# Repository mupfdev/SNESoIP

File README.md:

# SNESoIP: The SNES Wi-Fi adapter

## Status

In the first revisions I made some design flaws.  Looking back, it's
difficult for me to understand why it worked so well.  However, this
time I want to make it technically correct.  Therefore is the project is
currently in a state of re-design.

## Introduction

The SNESoIP (SNES over IP) is a Wi-Fi adapter for the Super Nintendo
Entertainment System which is also known as Super NES, SNES or Super
Nintendo.  It is basically a fully bi-directional, open-source,
proof-of-concept, Wi-Fi adapter, designed to connect a SNES to another
console and/or a special network service.

Possible applications would be bulletin board systems, multi-user
dungeons, IRC, etc.

I'm not planning to build and/or sell these devices but the device
should be fairly easy to recreate.  Especially because I try to use
parts that are cheap and widely available.

I also highly recommend to use this project only in combination with a
flash cartridge like the [sd2snes](http://sd2snes.de/blog/) or the Super
Everdrive.

If you want to help with the further development of this project, join
us on our [Discord server](https://discord.gg/araBwyp) or in the
[Retro.Live community](https://discord.gg/TuBCs4H).

## Annotation

It's not the project's main goal to support existing SNES games.  It
rather provides the technology that can be used to develop custom
homebrew applications such as multi-user dungeons, bulletin board
systems, etc.

However, it is possible.

## Project History

The SNESoIP is, so to speak, my never-ending long-term project, which I
started on 29 July 2013 and have taken up again and again since then.

The last time I put the project down was shortly before the birth of my
son.  The following years were strenuous; the new role as family father,
the death of my best friend [Ertugrul
Söylemez](https://github.com/esoeylemez), and frankly, I never intended
to resume the project at all.  Nevertheless, the project had a big
impact on my life and was, in a manner of speaking, the foundation for
my career as a software developer for embedded systems.

As you can imagine, this project is personal. And I always had the urge
to finish what I started almost 6 years ago.

We'll see how it goes.

### Press and Media

[2013-10-03: SystemLinks (Archive)](https://web.archive.org/web/20160714125922/http://www.systemlinks.net/blog/snesoip-xband-of-21st-century/)  
[2013-09-28: POP (Archive)](https://web.archive.org/web/20131001152616/http://www.pop.com.br/games/wii/Jogue-online-no-seu-Super-Nintendo-com-o-SNESoIP-1001612.html)  
[2013-09-27: RetroNews](http://www.retroplayers.com.br/noticias/retronews-snesoip-a-volta-da-jogatina-online-ao-super-nintendo/)  
[2013-09-27: Retro Players](http://www.retroplayers.com.br/noticias/retronews-snesoip-a-volta-da-jogatina-online-ao-super-nintendo/)  
[2013-09-24: Cubed3](http://www.cubed3.com/news/19635/1/play-original-snes-games-online.html)  
[2013-09-24: Nintendo Life](https://www.nintendolife.com/news/2013/09/online_multiplayer_comes_to_the_super_nintendo_thanks_to_snesoip)  
[2013-09-23: Jeux vidéo (Archive)](https://web.archive.org/web/20140209130208/http://www.jvn.com/actualites/snesoip-le-modem-pour-super-nintendo-a1070900)  
[2013-09-23: Kotaku Australia](https://www.kotaku.com.au/2013/09/you-can-play-your-original-snes-online-dont-you-know/)  
[2013-09-20: Motherboard (Archive)](https://web.archive.org/web/20160514015628/https://motherboard.vice.com/blog/play-your-super-nintendo-online-thanks-to-this-open-source-hardware)  
[2013-09-18: RetroCollect](http://www.retrocollect.com/News/snesoip-brings-online-multiplayer-to-the-super-nintendo.html)  
[2013-09-18: Retro Game Network](http://www.retrogamenetwork.com/2013/09/18/snesoip-super-nintendo-entertainment-system-over-internet-protocol-takes-snes-games-online/)  
[2013-09-18: Retro Nintendo (Archive)](https://web.archive.org/web/20171027161636/http://www.retronintendo.be/2013/09/18/snesoip-online-multiplayer-voor-de-super-nintendo/)  
[2013-09-17: geekimpact.de (Archive)](https://web.archive.org/web/20131205052338/http://geekimpact.de/tech/snesoip-online-multiplayer-fur-das-super-nintendo/)  
[2013-09-14: Hackaday](https://hackaday.com/2013/09/14/snesoip-its-exactly-what-it-sounds-like/)  
[2013-09-03: Hackalizer](http://hackalizer.com/snesoip-puts-controller-net/)  
[2013-04-10: pantalytron (Archive)](https://web.archive.org/web/20160717075259/http://www.pantalytron.com/blog7.php/i-am-the-chosen-one)  

## Hardware

The new hardware design will be based on a ESP32 microcontroller by
Espressif Systems.

## Licence and Credits

This project is licenced under the "THE BEER-WARE LICENCE".

The IRC client is based on [sic](https://tools.suckless.org/sic/), an extremely simple IRC
client and is licenced under the terms of the MIT/X Consortium License.

See the file LICENCE.md for details.

"Nintendo" is a registered trademark of Nintendo of America Inc.

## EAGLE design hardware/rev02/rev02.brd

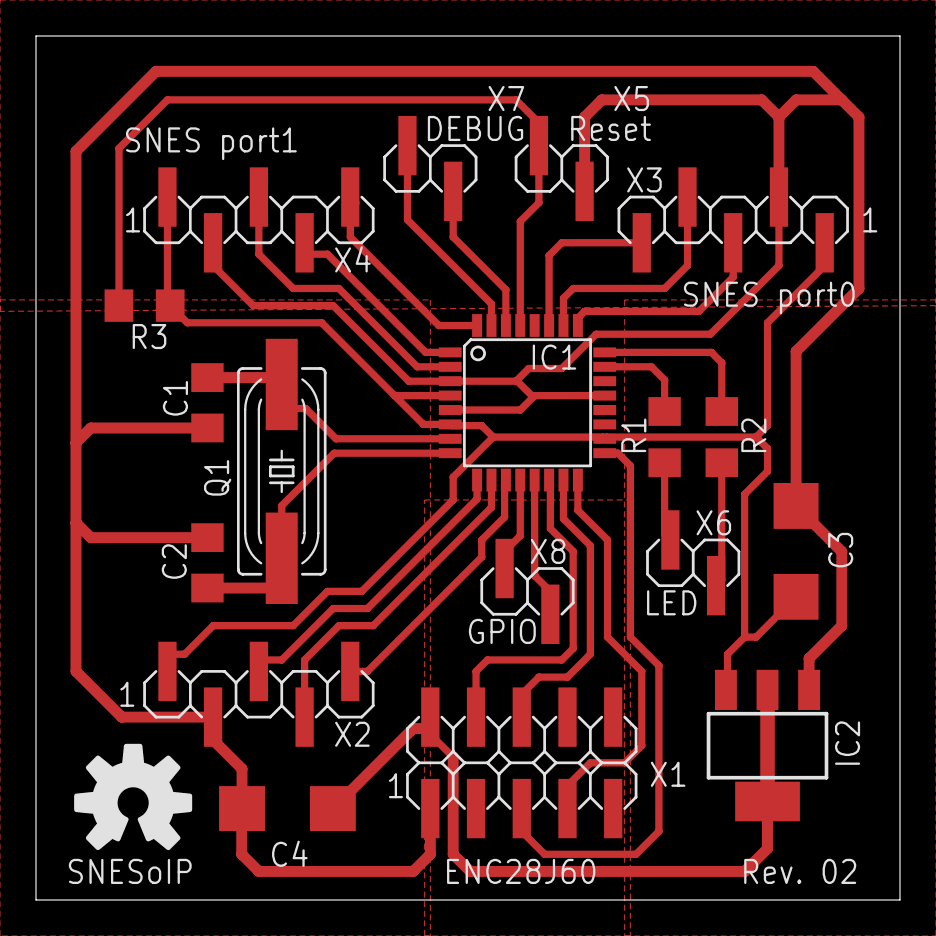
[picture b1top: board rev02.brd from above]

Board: 2 copper layers, 48.0 x 48.0 mm, 18 parts (0 on the bottom side), 27 nets.

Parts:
C1, C2: 22p; C1206
C3, C4: 10u; C/6032-28R
IC1: MEGA168; TQFP32-08
IC2: LD1117V33; SOT223
Q1: 16MHz; SM49
R1, R2: 220; R1206
R3: 10k; R1206
X1: ENC28J60; 2X05SMD
X2: SNES input; 1X05SMD
X3: SNES port0; 1X05SMD
X4: SNES port1; 1X05SMD
X5: Reset; 1X02SMD
X6: LED; 1X02SMD
X7: DEBUG; 1X02SMD
X8: GPIO; 1X02SMD

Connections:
+3V3: C4.+, IC2.2, IC2.TAB, X1.2
+5V: C3.+, IC1.4, IC1.6, IC1.18, IC2.3, R3.2, X2.1, X3.1, X4.1
CS: IC1.14, X1.4
GND: C1.2, C2.2, C3.-, C4.-, IC1.3, IC1.5, IC1.21, IC2.1, X1.1, X2.2, X3.2, X4.2, X5.1
GPIO0: IC1.12, X8.1
GPIO1: IC1.13, X8.2
INPUT-CLOCK: IC1.9, X2.3
INPUT-DATA: IC1.11, X2.5
INPUT-LATCH: IC1.10, X2.4
LED-GN: IC1.23, R1.1
LED-RD: IC1.24, R2.1
MISO: IC1.16, X1.7
MOSI: IC1.15, X1.6
unnamed: R2.2, X6.2
unnamed: R1.2, X6.1
unnamed: C1.1, IC1.7, Q1.2
unnamed: C2.1, IC1.8, Q1.1
PORT0-CLOCK: IC1.25, X3.3
PORT0-DATA: IC1.27, X3.5
PORT0-LATCH: IC1.26, X3.4
PORT1-CLOCK: IC1.2, X4.3
PORT1-DATA: IC1.32, X4.5
PORT1-LATCH: IC1.1, X4.4
RESET: IC1.29, R3.1, X5.2
RXD: IC1.30, X7.1
SCK: IC1.17, X1.5
TXD: IC1.31, X7.2

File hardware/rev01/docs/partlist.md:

# Partlist #

## Pin headers ##

- 1x 2x5 SMT (X1)
- 3x 1x5 SMT (X2, X3, X4)
- 2x 1x2 SMT (X5, X6)

## Capacitors ##
- 2x 22pF KER 1206 (C1, C2)
- 2x 10uF TAN C-6032 (C3, C4)

## Resistors ##
- 2x 220 1206 (R1, R2)
- 1x 10k 1206 (R3)

## Semiconductors ##

- 1x ATmega8 TQFP-32 (IC1)
- 1x LM1117 3.3V SOT-223 (IC2)

## External components ##

- 1x 2x5 Ribbon cable with IDC connectors (X1)
- 1x [ENC28J60 module](enc28j60-module.jpg) from [eBay](http://www.ebay.com/sch/?_nkw=enc28j60)
- 3x 1x5 Female header (X2, X3, X4)
- 2x 1x2 Female header (X5, X6)
- 1x [SNES controller connector](http://www.raphnet-tech.com/products/snes_controller_connect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
  or something appropriate (X2)
- 2x SNES controller plug (e.g. from an extension cable or cheap 3rd
  party controller) (X3, X4)
- 1x Tactile switch (X5)
- 1x Bi-Color LED rd/gn (X6)

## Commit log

2013-09-02 Initial version.
2013-09-02 Fixed donate link.
2013-09-02 Fixed some wrong indentation.
2013-09-02 Removed unused code line.
2013-09-02 Added female headers.
2013-09-02 Added missing word.
2013-09-02 Removed unneeded variable 'requestCache'.
2013-09-02 Fixed a typo.
2013-09-02 Added SNES controller connector/plug.
2013-09-02 Because I'm meticulous.
2013-09-02 Fixed missing character.
2013-09-02 Added image.
2013-09-03 Added link to the partlist.
2013-09-03 Correction in the communication protocol specification.
2013-09-03 Removed unused includes.
2013-09-04 Added SNES PS/2 keyboard adapter.
2013-09-04 Consistency for the win.
2013-09-04 Removed unused Phony targets.
2013-09-04 Added image. Fixed Makefile. Minor code cleanup.
2013-09-05 Moved 'prototype-small.jpg' to 'hardware/images'.
2013-09-05 Moved 'addon' to 'add-ons'.
2013-09-06 Added configuration utility.
2013-09-06 Adjusted max length of ServerVHost.
2013-09-06 Adjusted output message.
2013-09-06 Added 'firmware-untested'.
2013-09-06 Added IRC link.
2013-09-06 Changed phrasing.
2013-09-06 Minor fix.
2013-09-08 Moved 'firmware-untested' to 'firmware-dev'.
2013-09-08 Added missing counter.
2013-09-08 Added notice.
2013-09-09 Added GBoIP reference.
2013-09-14 Changed heading.
2013-10-02 Added wiki link.
2013-12-20 Added Windows binary.
2013-12-22 firmware-dev removed.
2013-12-23 server-dev added.
2013-12-23 Added demo link.
2013-12-23 Fixed demo link.
2013-12-23 Fixed wrong indentation.
2013-12-23 Reorganised folder structure.
2013-12-23 Added firmware placeholder.
2013-12-23 Marked config utility as obsolete.
2013-12-23 Added template for profile page.
2013-12-23 Added E-Mail field.
2013-12-23 Added foot note.
2013-12-23 Switched to php.
2013-12-23 Fixed broken link.
2013-12-28 testrom1 plus server added.
2013-12-29 testrom2 plus server added.
2013-12-29 Duplicate folder removed.
2013-12-30 Added unfinished server code.
2013-12-30 Minor code simplifications.
2013-12-30 Added MySQL init routines.
2013-12-30 Minor changes.
2013-12-31 Removed directory.
2013-12-31 Added placeholder for upcoming web interface.
2013-12-31 Removed testing folder.
2013-12-31 Minor firmware changes.
2013-12-31 Minor source code reorganisation.
2013-12-31 Added link to master branch.
2013-12-31 Fixed typo.
2013-12-31 Removed obsolete code.
2013-12-31 Added README.md.
2013-12-31 Minor code changes and cleanup.
2013-12-31 Minor cleanup.
2014-01-02 Initial version of the SNESoIP webinterface
    Early alpha version, for testing only
2014-01-02 Minor changes and updated file headers.
2014-01-02 Added credit.
2014-01-02 Added requirements.
2014-01-03 Cleanup and updated legal notes.
2014-01-03 Renamed LICENSE and AUTHORS.
2014-01-03 Okay, last commit didn't worked out.
2014-01-05 Added missing part (Q1).
2014-01-07 Removed obsolete source code.
2014-01-08 Update of file headers and removal of unnecessary code
2014-01-18 Implementation of the avatar feature, creating a small helpfile, fix of issue #4
2014-01-18 A little bit of Source cleanup
2014-08-03 Migration to hardware revision 02.
2014-08-03 Added PL2303 USB to Serial driver for Windows.
2014-08-06 Upgrade to latest TCP/IP stack.
2014-08-09 Added UART functionality.
2014-08-09 Fixed weird bug of yet unknown reason.
2014-08-09 Minor update.
2014-08-10 Final commit to old firmware.
2014-08-10 Initial commit (testing branch).
2014-08-17 Backup of current progress.
2014-08-19 Daily backup.
2014-08-20 For debugging purposes only.
2014-08-23 Backup of current progress. Nothing special.
2014-08-24 Added a minimalistic UART interface.
2014-08-24 Added option to hide progress bar.
2014-08-24 Minor backup.
2014-08-25 Added some images of rev02 hardware.
2014-08-26 Added simple command-line interface.
2014-08-27 Added correct backspace behavior.
2014-08-27 Updated command-line interface.
2014-08-27 Minor correction.
2014-08-28 Minor bug fix.
2014-08-28 Backup.
2014-08-30 execCommand() updated.
2014-08-30 Pre-bedtime backup. ;-)
2014-08-31 Minor bug fix (UART interface).
2014-08-31 Added small image for README.md
2014-08-31 Call me Monk.
2014-08-31 Copy & Paste fail.
2014-09-13 First TCP tests and some cleanup.
2014-09-13 Cleanup.
2014-09-14 Figured out how to use the TCP client.
2014-09-14 Removed leftover.
2014-09-21 Major cleanup.
2014-09-21 Added CLI documentation.
2014-09-21 Added current server version.
2014-09-21 Added virtual snesoip userspace device.
2014-09-23 Added socat tcp/udp gateway script plus moved port setting to the config file.
2014-09-23 Added timeout.
2014-09-23 Added headline in config.
2014-09-23 Typo.
2014-09-24 Added UDP listener
2014-09-26 Added simple CTC mode timer routine plus some minor code cleanup.
2014-09-27 Added an ascii text reader.
2014-09-27 Declared 2nd server prototype as obsolete.
2014-09-27 Added screenshot.
2014-09-27 Updated README.md.
2014-09-28 Added snes homebrew project skeleton.
2014-10-01 Added basic WRIO functionality.
2014-10-03 Added connector modification instructions.
2014-10-03 Added missing image.
2014-10-04 Added assembly instructions.
2014-10-05 Updated assembly instructions.
2015-10-07 Fix typographical error(s)
    Changed continous to continuous in README.
2019-04-14 Reorganise repository, add firmware template
2019-04-14 Update .gitignore and README.md, Add WIZnet W5100 driver
2019-04-14 Fix typo
2019-04-18 Replace STM32F103C8 FreeRTOS code with basic ESP32 equivalent
2019-04-18 Add Discord server invite to README.md
2019-04-19 Add Press and Media section
2019-04-19 Update formatting
2019-04-19 Update WiFi driver to work with SmartConfig
2019-04-19 Add README.md to Firmware
2019-04-20 Update documentation of unfinished SNES I/O driver
2019-04-20 Fix typo, add clarification
2019-04-25 Add TCP server to use as a terminal interface
2019-04-28 Add Zombies Ate My Neighbors patch
2019-04-28 Rename asar file to asm, fix notation
2019-04-28 Add RMT signal generator (test)
2019-05-01 Add main server application, unfinished
2019-05-01 Add README.md to ROMs sub-directory, add CI script to test firmware, minor cleanup
2019-05-01 Add CI badge to firmware readme
2019-05-01 Add temporary protocol description, add interrupt handler to catch CTRL+c
2019-05-01 Enable graphviz image generation, optimise output for C, add index.html as alternate entry point
2019-05-02 Update protocol description
2019-05-03 Connection handler: use threads instead of multiple processes
2019-05-03 Add basic client/server command handling
2019-05-05 Add logo, change description from ethernet to Wi-Fi adapter
2019-05-05 Add missing logo image file
2019-05-05 Add Zombies Ate My Neighbors label draft
2019-05-06 Update logo and Zombies Ate My Neighbors label
2019-05-06 Add CommonInclude, minor update on server code
2019-05-06 Add README.md to Tools sub-directory
2019-05-07 Update CommonInclude and connection handler
2019-05-08 Add IP exchange to connection handler
2019-05-08 Reorganise build scripts for server
2019-05-08 Add default.nix to compile the server on NixOS
2019-05-12 Update SNES I/O driver; the controller data is now read correctly. Add optional debug output
2019-05-12 Documentation: Update logic level converter to one that has been tested
2019-05-13 Clarify the fluctuation-problem because it isn't actually caused by mechanical switch bouncing
2019-05-13 Update TCP client and add basic client/server communication
2019-05-14 Update client/server IP exchange protocol, implement basic communication for IP exchange, add Zombies label (print approval), add template for SnIRC - the SNES IRC client
2019-05-14 Add missing newline
2019-05-14 Reorganise code base, adjust ports, driver names, etc.
2019-05-14 Increase stack size for client thread because of an unexpected stack overflow
2019-05-17 Add static test signal and ISR to send data from the MCU to the console
2019-05-19 Add basic but yet unfinished SPI configuration
2019-05-22 Backup latest changes in SNES driver
2019-06-02 Update LICENCE and README
2019-06-02 Rename generic client to IP exchange client
2019-06-02 Comment out unavailable function call
2019-06-02 Update README layout
2019-06-02 Update logo size in README
2019-06-06 Add SPI slave routine
